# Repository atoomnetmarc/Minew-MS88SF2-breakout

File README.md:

This is a simple breakout board for the nRF52840 Minew MS88SF2 module.

# Assembly instructions

Solder all components except the module. Clean PCB.

Test if 3V3 regulator works by connecting 5V to VIN5V-pin (with 50mA power limit). The board should not use any significant current. Measure the 3V3O-pin, it should be 3.3V.

Now solder module.

Do not forget to connect an antenna if using the MS88SF2-U.FL module.

# Checklist (WIP) V1.0 PCB

Testing and working? (after bodge fix, see V1.1 changelog)

:ballot_box_with_check:SWD (SWDIO, SWCLK, SWO)\
:ballot_box_with_check:RESET (P0.18)\
:ballot_box_with_check:USB\
:black_square_button:NFC (P0.09, P0.10)\
:black_square_button:P0.02\
:black_square_button:P0.04\
:ballot_box_with_check:LED green (P0.06)\
:black_square_button:LED RGB red (P0.08)\
:ballot_box_with_check:LED RGB blue (P0.12)\
:black_square_button:P0.13\
:black_square_button:P0.15\
:black_square_button:P0.20\
:black_square_button:P0.22\
:black_square_button:P0.24\
:black_square_button:P0.26\
:black_square_button:P0.29\
:black_square_button:P0.31\
:ballot_box_with_check:LED RGB green (P1.09)\
:black_square_button:Button (P1.13)\
:black_square_button:P1.15

# Changelog

**V1.1**

- Attached VDDH to VBUS to enable USB to work.
- Removed series resistors from USB data lines.

**V1.0**

- Everything changed out of nothing.

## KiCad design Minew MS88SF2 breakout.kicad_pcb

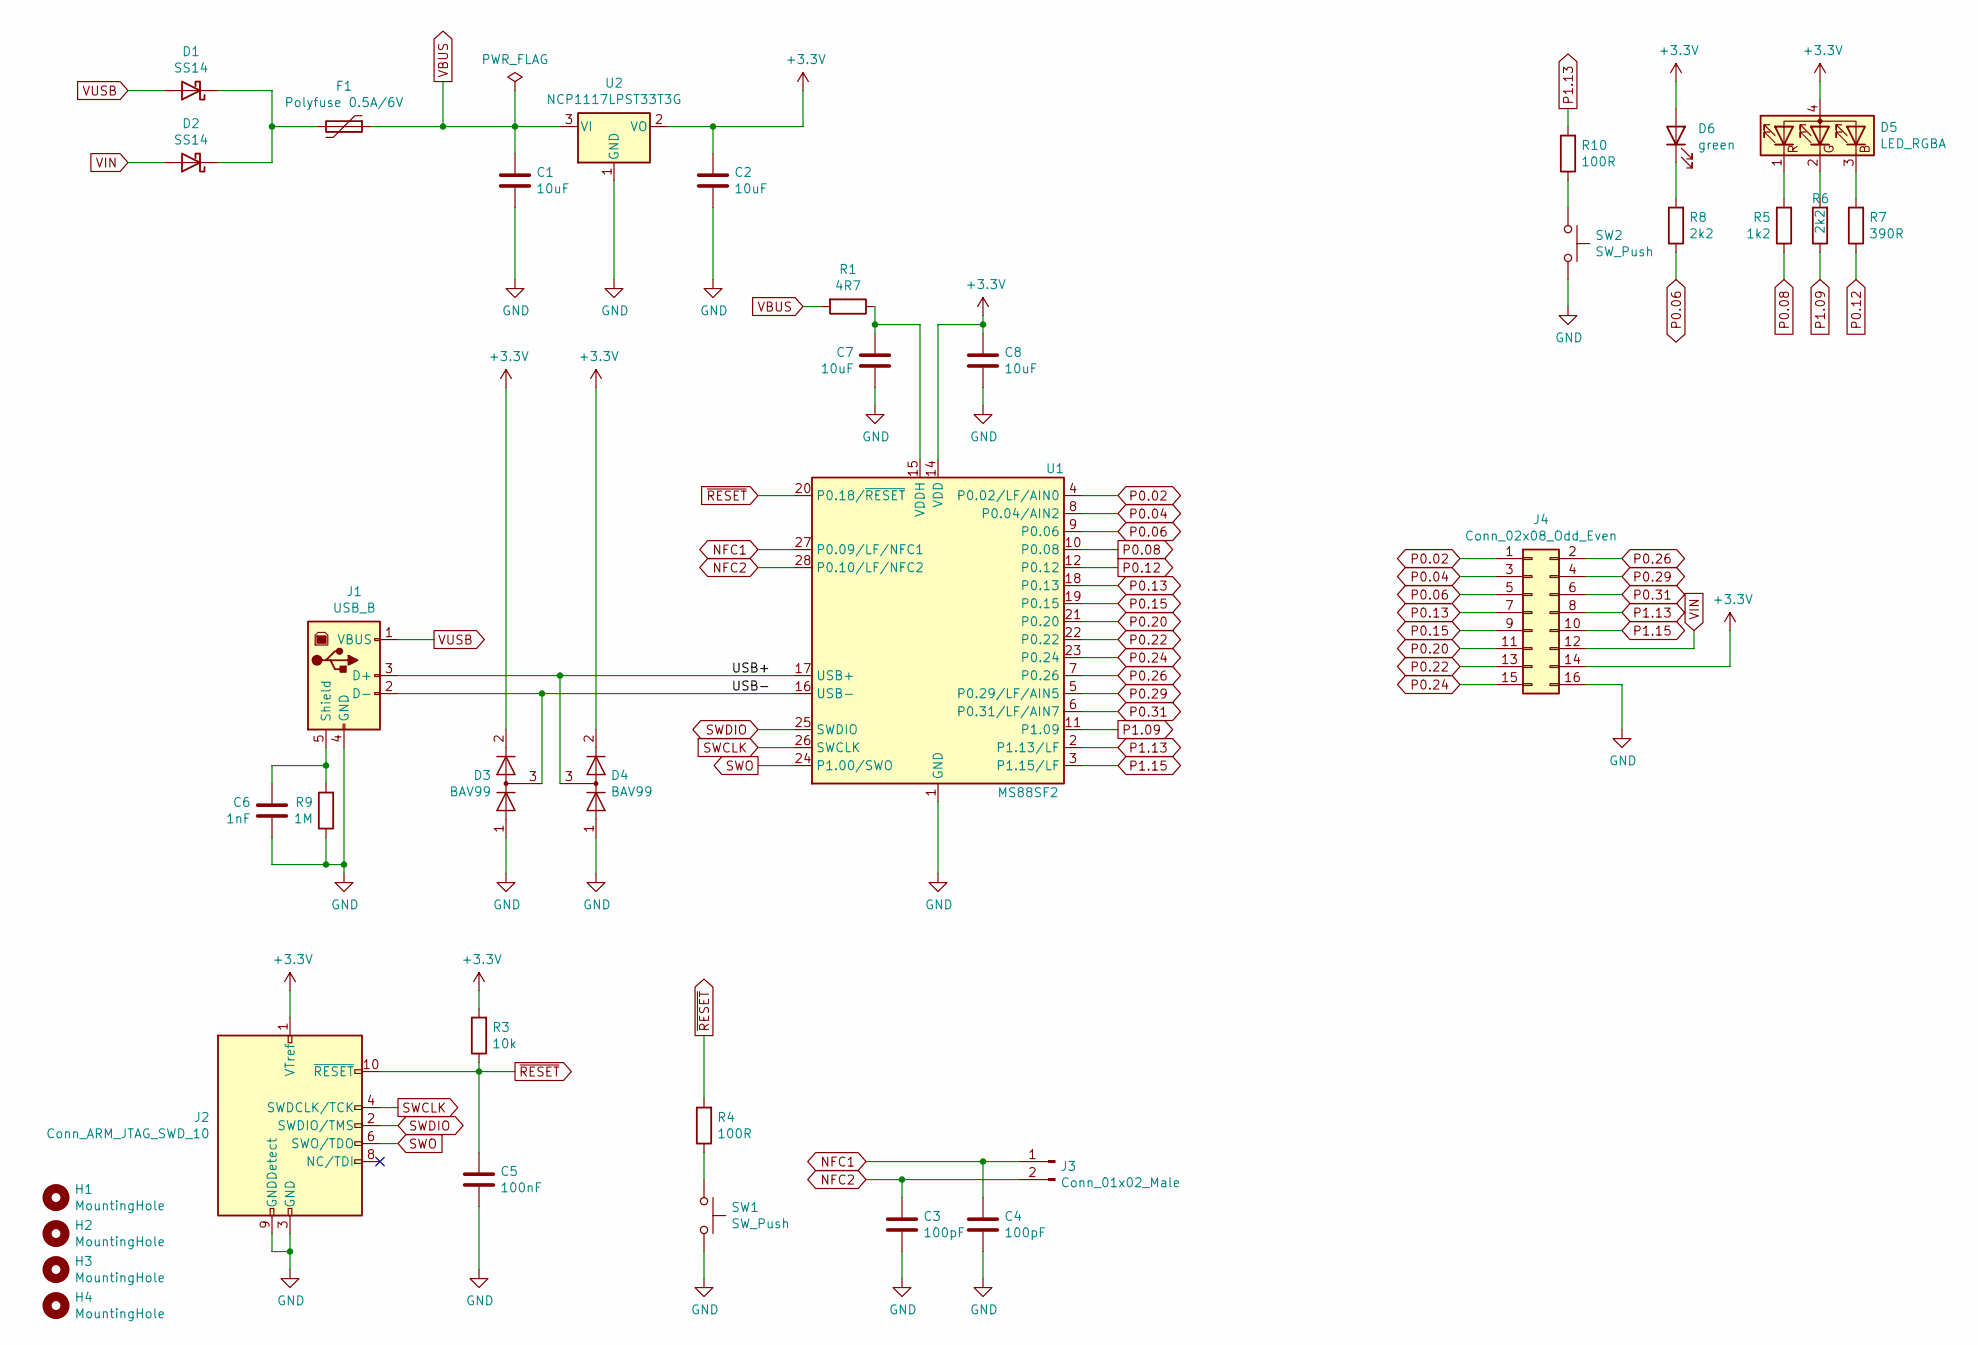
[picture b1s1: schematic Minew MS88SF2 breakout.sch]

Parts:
C1, C2, C7, C8: 10uF; C_0805_2012Metric_Pad1.18x1.45mm_HandSolder
C3, C4: 100pF; C_0805_2012Metric_Pad1.18x1.45mm_HandSolder
C5: 100nF; C_0805_2012Metric_Pad1.18x1.45mm_HandSolder
C6: 1nF; C_0805_2012Metric_Pad1.18x1.45mm_HandSolder
D1, D2: SS14; D_SMA
D3, D4: BAV99; SOT-23
D5: LED_RGBA; LED_RGB_3528
D6: green; LED_0805_2012Metric_Pad1.15x1.40mm_HandSolder
F1: Polyfuse 0.5A/6V; Fuse_1206_3216Metric_Pad1.42x1.75mm_HandSolder
H1, H2, H3, H4: MountingHole; MountingHole_3.5mm
J1: USB_B; USB_B_OST_USB-B1HSxx_Horizontal
J2: Conn_ARM_JTAG_SWD_10; PinHeader_2x05_P2.54mm_Vertical
J3: Conn_01x02_Male; PinHeader_1x02_P2.54mm_Vertical
J4: Conn_02x08_Odd_Even; PinHeader_2x08_P2.54mm_Vertical
R1: 4R7; R_0805_2012Metric_Pad1.20x1.40mm_HandSolder
R3: 10k; R_0805_2012Metric_Pad1.20x1.40mm_HandSolder
R4, R10: 100R; R_0805_2012Metric_Pad1.20x1.40mm_HandSolder
R5: 1k2; R_0805_2012Metric_Pad1.20x1.40mm_HandSolder
R6, R8: 2k2; R_0805_2012Metric_Pad1.20x1.40mm_HandSolder
R7: 390R; R_0805_2012Metric_Pad1.20x1.40mm_HandSolder
R9: 1M; R_0805_2012Metric_Pad1.20x1.40mm_HandSolder
SW1, SW2: SW_Push; SW_SPST_CK_RS282G05A3
U1: MS88SF2; MS88SF2-handsolder
U2: NCP1117LPST33T3G; SOT-223-3_TabPin2

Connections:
+3V3: C2.1, C8.1, D3.2 (A), D4.2 (A), D5.4 (A), D6.2 (A), J2.1 (VTref), J4.14, R3.2, U1.14 (VDD), U2.2 (VO)
/USB+: D4.3 (K), J1.3 (D+), U1.17 (USB+)
/USB-: D3.3 (K), J1.2 (D-), U1.16 (USB-)
GND: C1.2, C2.2, C3.2, C4.2, C5.2, C6.2, C7.2, C8.2, D3.1 (K), D4.1 (K), J1.4 (GND), J2.3 (GND), J2.5 (GND), J2.9 (GNDDetect), J4.16, R9.1, SW1.2, SW2.2, U1.1 (GND), U1.13 (GNDA), U2.1 (GND)
NFC1: C4.1, J3.1, U1.27 (P0.09/LF/NFC1)
NFC2: C3.1, J3.2, U1.28 (P0.10/LF/NFC2)
unnamed: C6.1, J1.5 (Shield), R9.2
unnamed: C7.1, R1.1, U1.15 (VDDH)
unnamed: D1.1 (K), D2.1 (K), F1.2
unnamed: D5.1 (RK), R5.2
unnamed: D5.2 (GK), R6.2
unnamed: D5.3 (BK), R7.2
unnamed: D6.1 (K), R8.2
unnamed: R4.1, SW1.1
unnamed: R10.1, SW2.1
P0.02: J4.1, U1.4 (P0.02/LF/AIN0)
P0.04: J4.3, U1.8 (P0.04/AIN2)
P0.06: J4.5, R8.1, U1.9 (P0.06)
P0.08: R5.1, U1.10 (P0.08)
P0.12: R7.1, U1.12 (P0.12)
P0.13: J4.7, U1.18 (P0.13)
P0.15: J4.9, U1.19 (P0.15)
P0.20: J4.11, U1.21 (P0.20)
P0.22: J4.13, U1.22 (P0.22)
P0.24: J4.15, U1.23 (P0.24)
P0.26: J4.2, U1.7 (P0.26)
P0.29: J4.4, U1.5 (P0.29/LF/AIN5)
P0.31: J4.6, U1.6 (P0.31/LF/AIN7)
P1.09: R6.1, U1.11 (P1.09)
P1.13: J4.8, R10.2, U1.2 (P1.13/LF)
P1.15: J4.10, U1.3 (P1.15/LF)
SWCLK: J2.4 (SWDCLK/TCK), U1.26 (SWCLK)
SWDIO: J2.2 (SWDIO/TMS), U1.25 (SWDIO)
SWO: J2.6 (SWO/TDO), U1.24 (P1.00/SWO)
VBUS: C1.1, F1.1, R1.2, U2.3 (VI)
VIN: D2.2 (A), J4.12
VUSB: D1.2 (A), J1.1 (VBUS)
~RESET: C5.1, J2.10 (~RESET~), R3.1, R4.2, U1.20 (P0.18/~RESET)

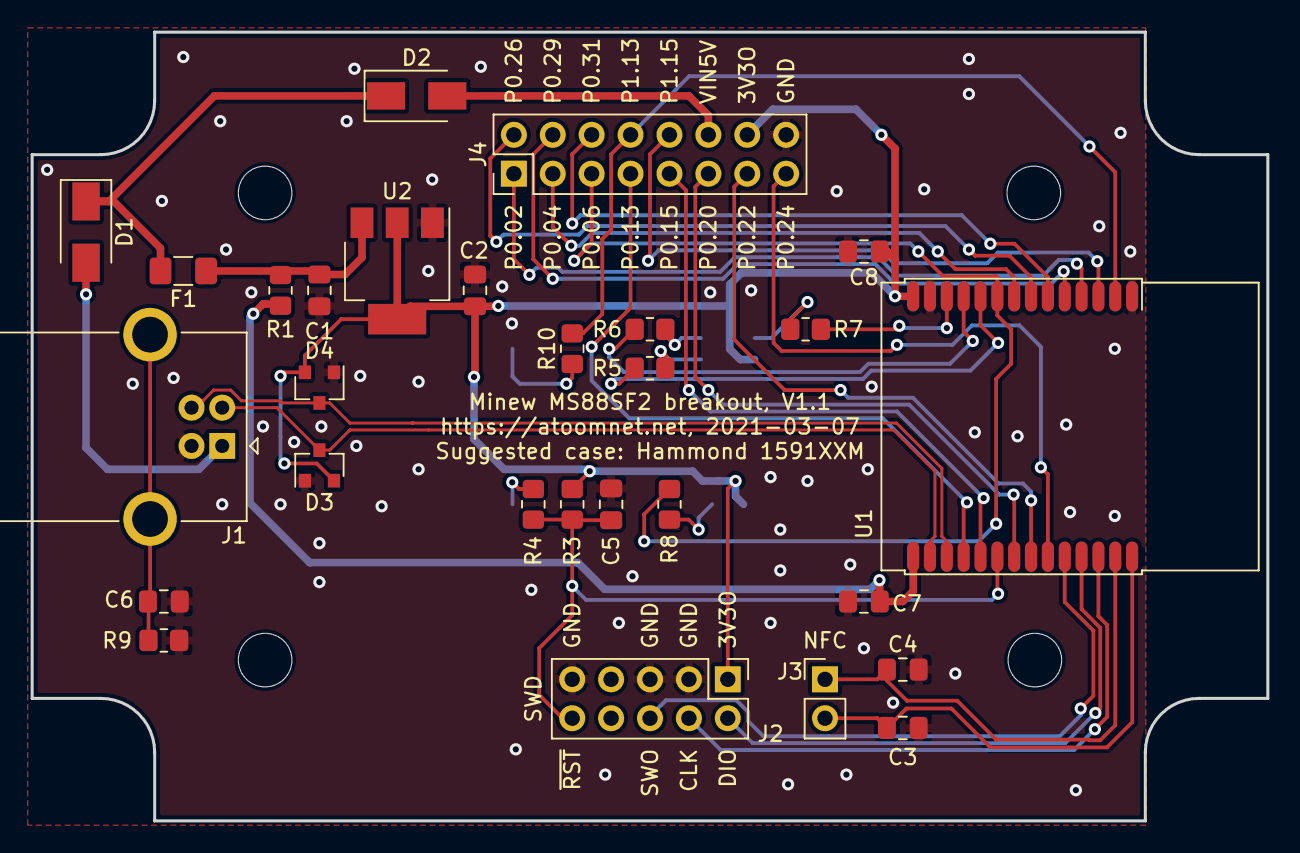
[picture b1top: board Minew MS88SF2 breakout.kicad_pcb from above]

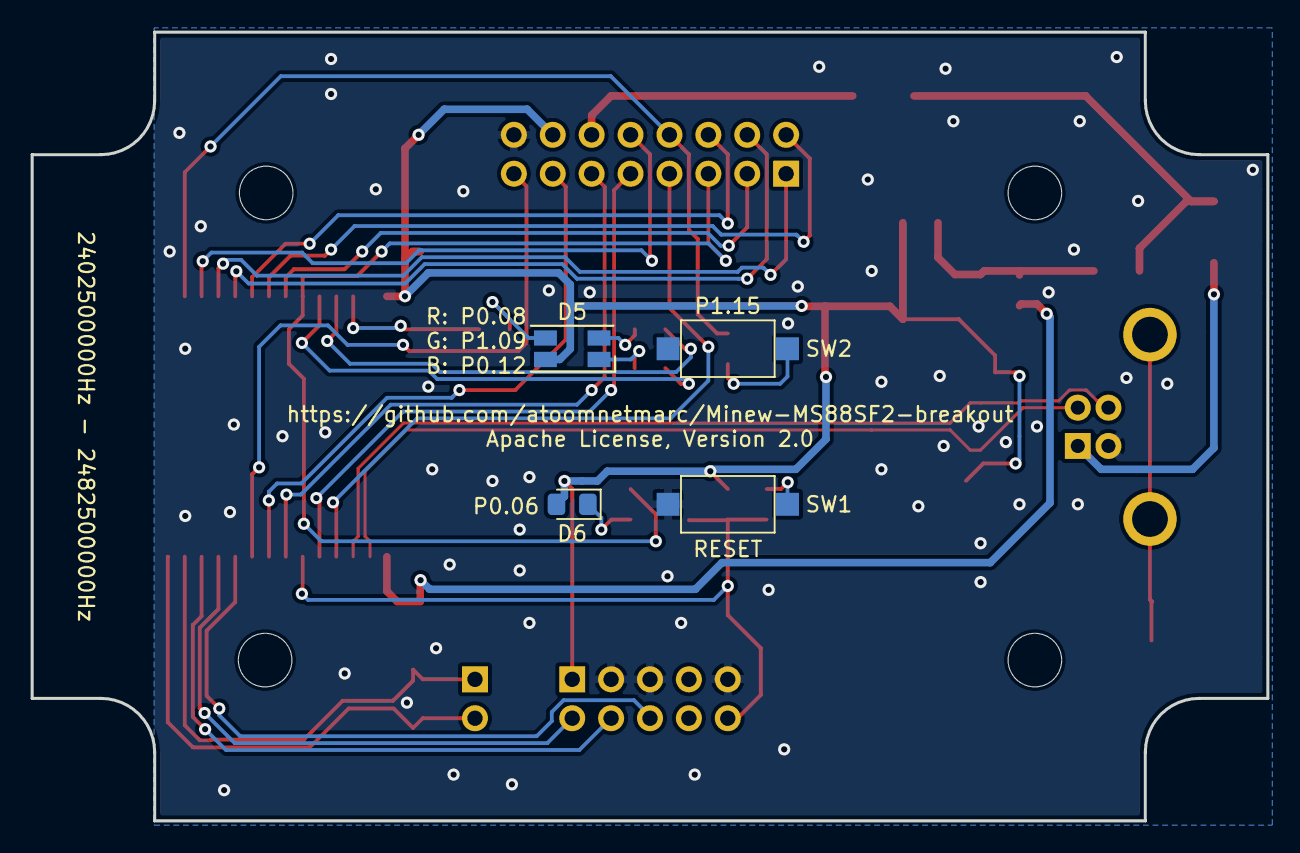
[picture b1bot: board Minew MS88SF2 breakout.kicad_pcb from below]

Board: 2 copper layers, 80.7 x 51.5 mm, 36 parts (4 on the bottom side), 38 nets.

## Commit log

2026-01-23 Add CONTRIBUTING.md

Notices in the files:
Minew MS88SF2 breakout.kicad_pcb:
Apache License, Version 2.0
README.md:
License: Apache 2.0
